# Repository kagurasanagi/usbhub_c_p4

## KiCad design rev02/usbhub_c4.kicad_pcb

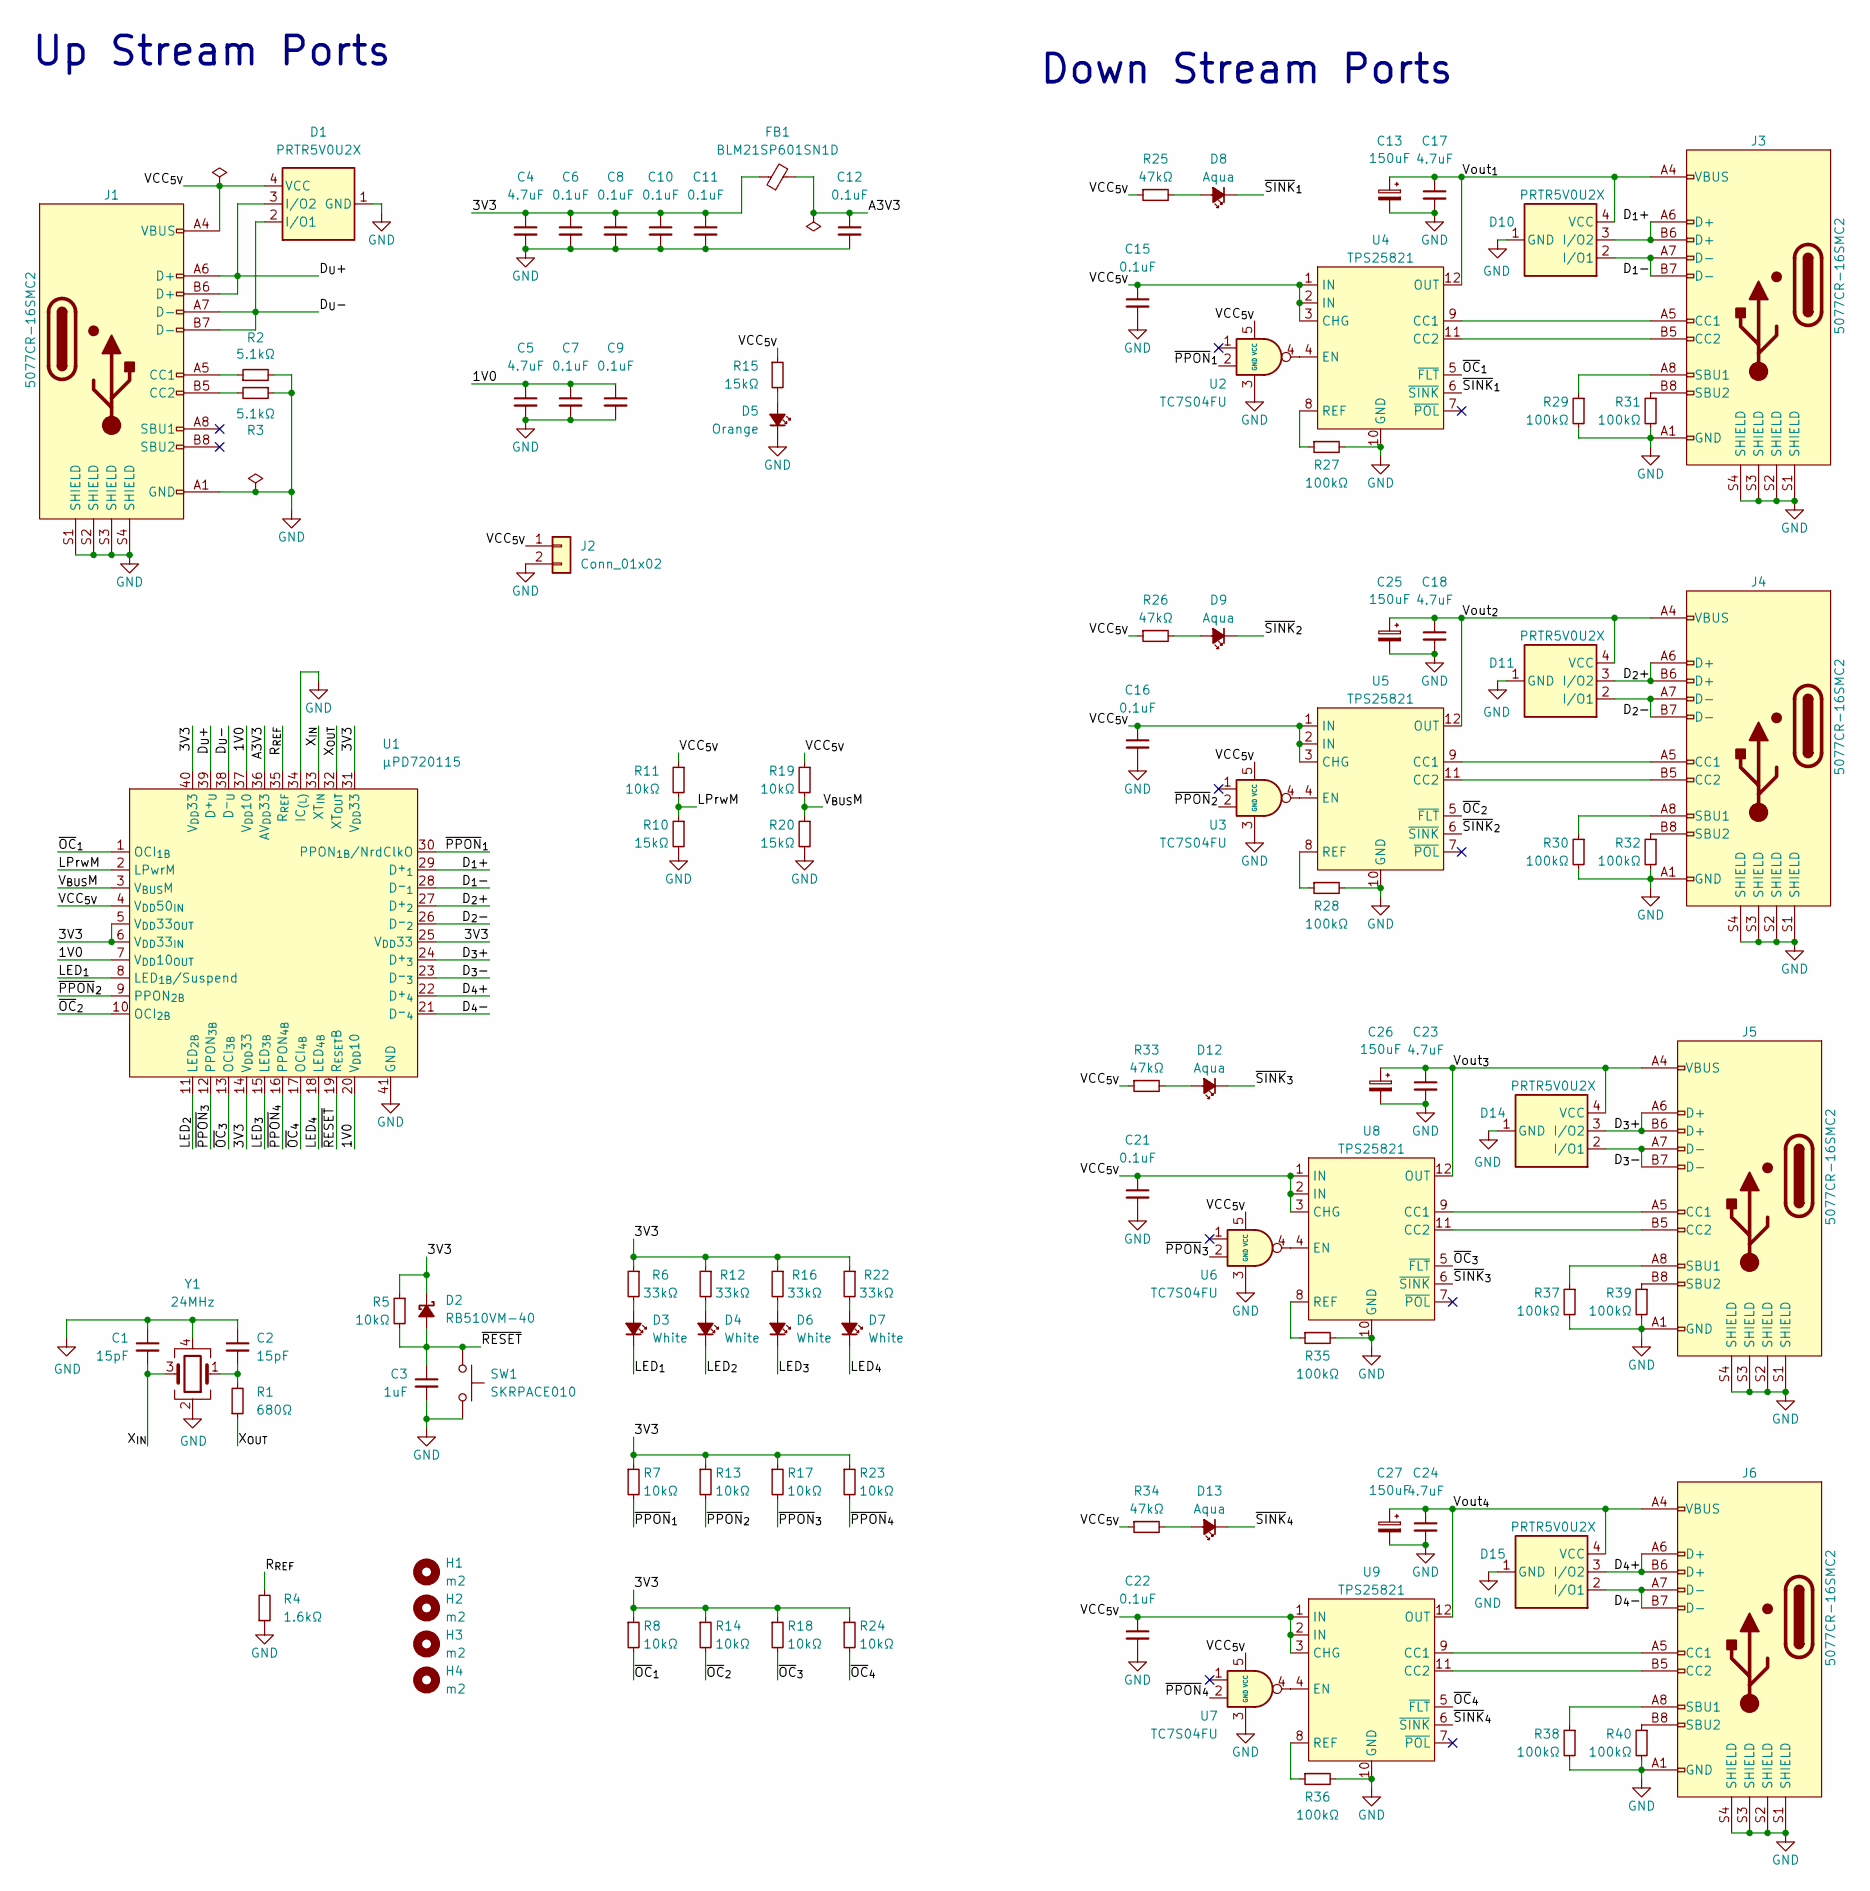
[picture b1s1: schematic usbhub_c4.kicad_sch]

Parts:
C1, C2: 15pF; C_0603_1608Metric
C3: 1uF; C_0603_1608Metric
C4, C5, C17, C18, C23, C24: 4.7uF; C_1206_3216Metric
C6, C7, C8, C9, C10, C11, C12: 0.1uF; C_0402_1005Metric
C13, C25, C26, C27: 150uF; CP_Radial_D6.3mm_P2.50mm
C15, C16, C21, C22: 0.1uF; C_0603_1608Metric
D1, D10, D11, D14, D15: PRTR5V0U2X; SOT-143
D2: RB510VM-40; Rohm_UMD2
D3, D4, D6, D7: White; LED_0603_1608Metric
D5: Orange; LED_0603_1608Metric
D8, D9, D12, D13: Aqua; LED_0603_1608Metric
FB1: BLM21SP601SN1D; R_0805_2012Metric
H1, H2, H3, H4: m2; MountingHole_2.2mm
J1, J3, J4, J5, J6: 5077CR-16SMC2; USB_C_Receptacle_5077CR-16SMC2
J2: Conn_01x02; JST_PH_B2B-PH-K_1x02_P2.00mm_Vertical
R1: 680Ω; R_0402_1005Metric
R2, R3: 5.1kΩ; R_0603_1608Metric
R4: 1.6kΩ; R_0402_1005Metric
R5, R11, R19: 10kΩ; R_0603_1608Metric
R6, R12, R16, R22: 33kΩ; R_0603_1608Metric
R7, R8, R13, R14, R17, R18, R23, R24: 10kΩ; R_0402_1005Metric
R10, R15, R20: 15kΩ; R_0603_1608Metric
R25, R26, R33, R34: 47kΩ; R_0603_1608Metric
R27, R28, R29, R30, R31, R32, R35, R36, R37, R38, R39, R40: 100kΩ; R_0603_1608Metric
SW1: SKRPACE010; SW_Push_1P1T_alps_SKRP
U1: μPD720115; QFN-40-1EP_6x6mm_P0.5mm_EP4.6x4.6mm
U2, U3, U6, U7: TC7S04FU; SOT-353_SC-70-5
U4, U5, U8, U9: TPS25821; WSON-12-1EP_3x2mm_P0.5mm_EP1x2.65_ThermalVias
Y1: 24MHz; Crystal_SMD_SeikoEpson_TSX3225-4Pin_3.2x2.5mm

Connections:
/1V0: C5.1, C7.1, C9.1, U1.7 (V_{DD}10_{OUT}), U1.20 (V_{DD}10), U1.37 (V_{DD}10)
/3V3: C4.1, C6.1, C8.1, C10.1, C11.1, D2.1 (K), FB1.1, R5.1, R6.1, R7.1, R8.1, R12.1, R13.1, R14.1, R16.1, R17.1, R18.1, R22.1, R23.1, R24.1, U1.5 (V_{DD}33_{OUT}), U1.6 (V_{DD}33_{IN}), U1.14 (V_{DD}33), U1.25 (V_{DD}33), U1.31 (V_{DD}33), U1.40 (V_{DD}33)
/A3V3: C12.1, FB1.2, U1.36 (AV_{DD}33)
/D_{1}+: D10.3 (I/O2), J3.A6 (D+), J3.B6 (D+), U1.29 (D^{+}_{1})
/D_{1}-: D10.2 (I/O1), J3.A7 (D-), J3.B7 (D-), U1.28 (D^{-}_{1})
/D_{2}+: D11.3 (I/O2), J4.A6 (D+), J4.B6 (D+), U1.27 (D^{+}_{2})
/D_{2}-: D11.2 (I/O1), J4.A7 (D-), J4.B7 (D-), U1.26 (D^{-}_{2})
/D_{3}+: D14.3 (I/O2), J5.A6 (D+), J5.B6 (D+), U1.24 (D^{+}_{3})
/D_{3}-: D14.2 (I/O1), J5.A7 (D-), J5.B7 (D-), U1.23 (D^{-}_{3})
/D_{4}+: D15.3 (I/O2), J6.A6 (D+), J6.B6 (D+), U1.22 (D^{+}_{4})
/D_{4}-: D15.2 (I/O1), J6.A7 (D-), J6.B7 (D-), U1.21 (D^{-}_{4})
/D_{U}+: D1.3 (I/O2), J1.A6 (D+), J1.B6 (D+), U1.39 (D^{+}_{U})
/D_{U}-: D1.2 (I/O1), J1.A7 (D-), J1.B7 (D-), U1.38 (D^{-}_{U})
/LED_{1}: D3.1 (K), U1.8 (LED_{1B}/Suspend)
/LED_{2}: D4.1 (K), U1.11 (LED_{2B})
/LED_{3}: D6.1 (K), U1.15 (LED_{3B})
/LED_{4}: D7.1 (K), U1.18 (LED_{4B})
/LPrwM: R10.1, R11.2, U1.2 (LPwrM)
/R_{REF}: R4.2, U1.35 (R_{REF})
/VCC_{5V}: C15.1, C16.1, C21.1, C22.1, D1.4 (VCC), J1.A4 (VBUS), J1.B4 (VBUS), J2.1, R11.1, R15.1, R19.1, R25.1, R26.1, R33.1, R34.1, U1.4 (V_{DD}50_{IN}), U2.5 (VCC), U3.5 (VCC), U4.1 (IN), U4.2 (IN), U4.3 (CHG), U5.1 (IN), U5.2 (IN), U5.3 (CHG), U6.5 (VCC), U7.5 (VCC), U8.1 (IN), U8.2 (IN), U8.3 (CHG), U9.1 (IN), U9.2 (IN), U9.3 (CHG)
/V_{BUS}M: R19.2, R20.1, U1.3 (V_{BUS}M)
/Vout_{1}: C13.1, C17.1, D10.4 (VCC), J3.A4 (VBUS), J3.B4 (VBUS), U4.12 (OUT)
/Vout_{2}: C18.1, C25.1, D11.4 (VCC), J4.A4 (VBUS), J4.B4 (VBUS), U5.12 (OUT)
/Vout_{3}: C23.1, C26.1, D14.4 (VCC), J5.A4 (VBUS), J5.B4 (VBUS), U8.12 (OUT)
/Vout_{4}: C24.1, C27.1, D15.4 (VCC), J6.A4 (VBUS), J6.B4 (VBUS), U9.12 (OUT)
/X_{IN}: C1.2, U1.33 (XT_{IN}), Y1.3
/X_{OUT}: R1.1, U1.32 (XT_{OUT})
/~OC_{1}: R8.2, U1.1 (OCI_{1B}), U4.5 (~FLT)
/~OC_{2}: R14.2, U1.10 (OCI_{2B}), U5.5 (~FLT)
/~OC_{3}: R18.2, U1.13 (OCI_{3B}), U8.5 (~FLT)
/~OC_{4}: R24.2, U1.17 (OCI_{4B}), U9.5 (~FLT)
/~PPON_{1}: R7.2, U1.30 (PPON_{1B}/NrdClkO), U2.2
/~PPON_{2}: R13.2, U1.9 (PPON_{2B}), U3.2
/~PPON_{3}: R17.2, U1.12 (PPON_{3B}), U6.2
/~PPON_{4}: R23.2, U1.16 (PPON_{4B}), U7.2
/~RESET: C3.1, D2.2 (A), R5.2, SW1.1, U1.19 (R_{ESET}B)
/~SINK_{1}: D8.1 (K), U4.6 (~SINK)
/~SINK_{2}: D9.1 (K), U5.6 (~SINK)
/~SINK_{3}: D12.1 (K), U8.6 (~SINK)
/~SINK_{4}: D13.1 (K), U9.6 (~SINK)
GND: C1.1, C2.1, C3.2, C4.2, C5.2, C6.2, C7.2, C8.2, C9.2, C10.2, C11.2, C12.2, C13.2, C15.2, C16.2, C17.2, C18.2, C21.2, C22.2, C23.2, C24.2, C25.2, C26.2, C27.2, D1.1 (GND), D5.1 (K), D10.1 (GND), D11.1 (GND), D14.1 (GND), D15.1 (GND), J1.A1 (GND), J1.B1 (GND), J1.S1 (SHIELD), J1.S2 (SHIELD), J1.S3 (SHIELD), J1.S4 (SHIELD), J2.2, J3.A1 (GND), J3.B1 (GND), J3.S1 (SHIELD), J3.S2 (SHIELD), J3.S3 (SHIELD), J3.S4 (SHIELD), J4.A1 (GND), J4.B1 (GND), J4.S1 (SHIELD), J4.S2 (SHIELD), J4.S3 (SHIELD), J4.S4 (SHIELD), J5.A1 (GND), J5.B1 (GND), J5.S1 (SHIELD), J5.S2 (SHIELD), J5.S3 (SHIELD), J5.S4 (SHIELD), J6.A1 (GND), J6.B1 (GND), J6.S1 (SHIELD), J6.S2 (SHIELD), J6.S3 (SHIELD), J6.S4 (SHIELD), R2.2, R3.1, R4.1, R10.2, R20.2, R27.2, R28.2, R29.2, R30.2, R31.2, R32.2, R35.2, R36.2, R37.2, R38.2, R39.2, R40.2, SW1.2, U1.34 (IC_{(L)}), U1.41 (GND), U2.3 (GND), U3.3 (GND), U4.10 (GND), U4.13 (GND), U5.10 (GND), U5.13 (GND), U6.3 (GND), U7.3 (GND), U8.10 (GND), U8.13 (GND), U9.10 (GND), U9.13 (GND), Y1.2, Y1.4
unnamed: C2.2, R1.2, Y1.1
unnamed: D3.2 (A), R6.2
unnamed: D4.2 (A), R12.2
unnamed: D5.2 (A), R15.2
unnamed: D6.2 (A), R16.2
unnamed: D7.2 (A), R22.2
unnamed: D8.2 (A), R25.2
unnamed: D9.2 (A), R26.2
unnamed: D12.2 (A), R33.2
unnamed: D13.2 (A), R34.2
unnamed: J1.A5 (CC1), R2.1
unnamed: J1.B5 (CC2), R3.2
unnamed: J3.A5 (CC1), U4.9 (CC1)
unnamed: J3.B5 (CC2), U4.11 (CC2)
unnamed: J3.A8 (SBU1), R29.1
unnamed: J3.B8 (SBU2), R31.1
unnamed: J4.A5 (CC1), U5.9 (CC1)
unnamed: J4.B5 (CC2), U5.11 (CC2)
unnamed: J4.A8 (SBU1), R30.1
unnamed: J4.B8 (SBU2), R32.1
unnamed: J5.A5 (CC1), U8.9 (CC1)
unnamed: J5.B5 (CC2), U8.11 (CC2)
unnamed: J5.A8 (SBU1), R37.1
unnamed: J5.B8 (SBU2), R39.1
unnamed: J6.A5 (CC1), U9.9 (CC1)
unnamed: J6.B5 (CC2), U9.11 (CC2)
unnamed: J6.A8 (SBU1), R38.1
unnamed: J6.B8 (SBU2), R40.1
unnamed: U2.4, U4.4 (EN)
unnamed: R27.1, U4.8 (REF)
unnamed: U3.4, U5.4 (EN)
unnamed: R28.1, U5.8 (REF)
unnamed: U6.4, U8.4 (EN)
unnamed: R35.1, U8.8 (REF)
unnamed: U7.4, U9.4 (EN)
unnamed: R36.1, U9.8 (REF)

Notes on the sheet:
Up Stream Ports
Down Stream Ports

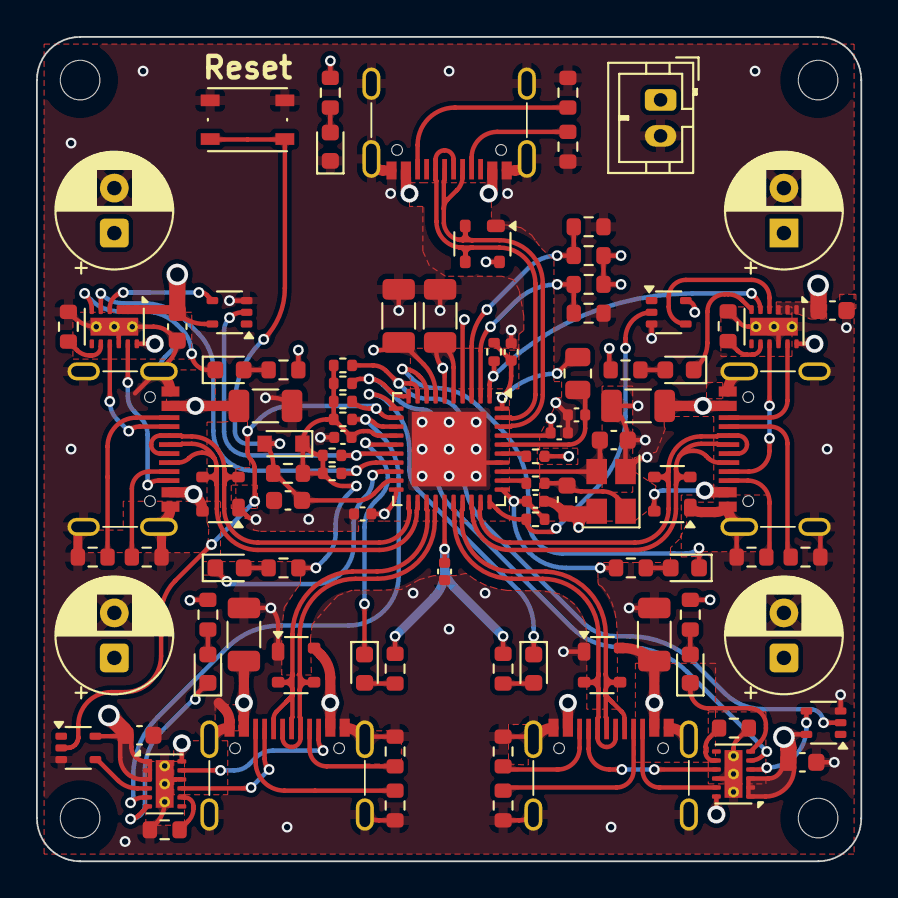
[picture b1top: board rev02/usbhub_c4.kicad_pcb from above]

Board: 4 copper layers, 45.8 x 45.8 mm, 99 parts (0 on the bottom side), 77 nets.

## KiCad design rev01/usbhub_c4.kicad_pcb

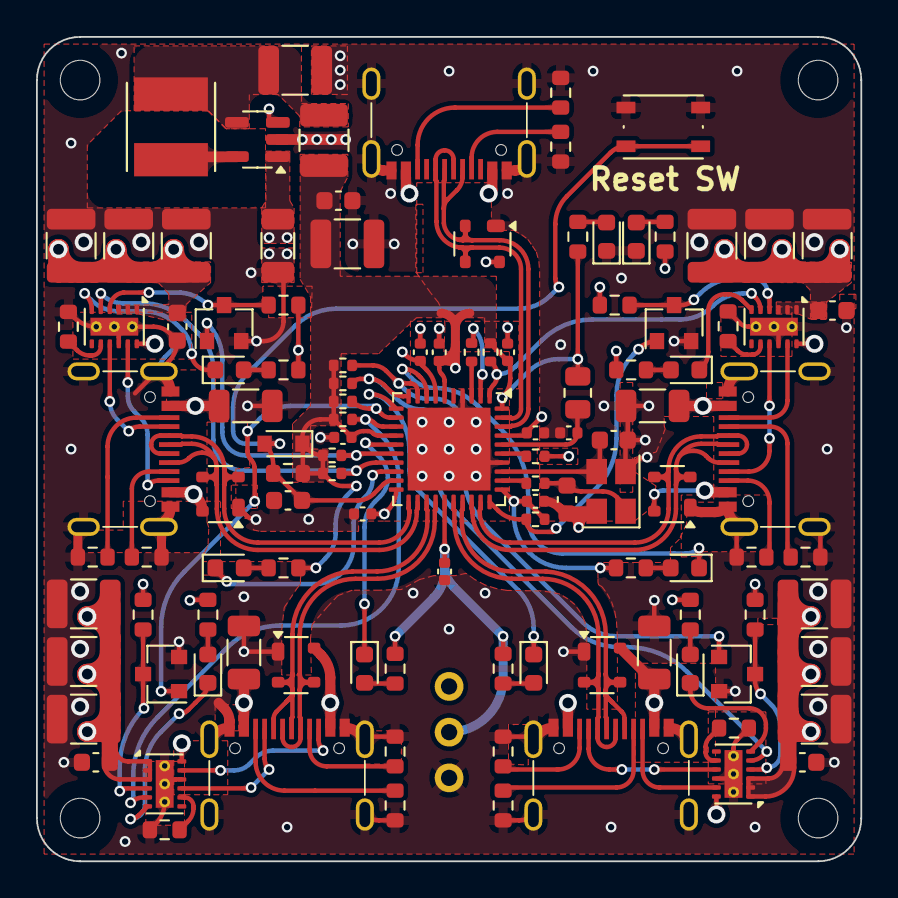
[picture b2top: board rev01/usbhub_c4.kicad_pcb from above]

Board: 4 copper layers, 45.8 x 45.8 mm, 119 parts (0 on the bottom side), 79 nets.

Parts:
C1, C21, C26, C31, C36: 4.7uF; C_1206_3216Metric
C2, C3, C17, C18, C19, C22, C23, C24, C27, C28, C29, C32, C33, C34: 47uF; C_1210_3225Metric
C4, C20, C25, C30, C35: 0.1uF; C_0603_1608Metric
C5, C6: 15pF; C_0603_1608Metric
C7: 1uF; C_0603_1608Metric
C8, C14: 4.7uF; C_0402_1005Metric
C9, C10, C11, C12, C13, C15, C16: 0.1uF; C_0402_1005Metric
D1, D10, D12, D14, D16: PRTR5V0U2X; SOT-143
D2: Orange; LED_0603_1608Metric
D3: Green; LED_0603_1608Metric
D4: RB510VM-40; Rohm_UMD2
D5, D6, D7, D8: White; LED_0603_1608Metric
D9, D11, D13, D15: WarmWhite; LED_0603_1608Metric
FB1: BLM21SP601SN1D; R_0805_2012Metric
H1, H2, H3, H4: m2; MountingHole_2.2mm
J1, J5, J6, J7, J8: 5077CR-16SMC2; USB_C_Receptacle_5077CR-16SMC2
J2, J3, J4: Conn_01x01; PinHeader_1x01_P2.54mm_Vertical
L1: 10uH; IND_LQH5BPN100M38L
L2: 1uH; L_1210_3225Metric
Q1, Q2, Q3, Q4: BSS138; SOT-23
R1, R2: 5.1kΩ; R_0603_1608Metric
R3: 15kΩ; R_0603_1608Metric
R4, R21, R26, R31, R36: 47kΩ; R_0603_1608Metric
R5: 680Ω; R_0402_1005Metric
R6: 10kΩ; R_0603_1608Metric
R7, R8, R9, R10: 33kΩ; R_0603_1608Metric
R11, R12, R13, R14, R15, R16, R17, R18, R19: 10kΩ; R_0402_1005Metric
R20: 1.6kΩ; R_0402_1005Metric
R22, R23, R24, R25, R27, R28, R29, R30, R32, R33, R34, R35, R37, R38, R39, R40: 100kΩ; R_0603_1608Metric
SW1: SKRPACE010; SW_Push_1P1T_alps_SKRP
U1: LM3670MF-3.3; TSOT-23-5
U2: μPD720115; QFN-40-1EP_6x6mm_P0.5mm_EP4.6x4.6mm
U3, U4, U5, U6: TPS25821; WSON-12-1EP_3x2mm_P0.5mm_EP1x2.65_ThermalVias
Y1: 24MHz; Crystal_SMD_SeikoEpson_TSX3225-4Pin_3.2x2.5mm

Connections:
/1V0: C14.1, C15.1, C16.1, U2.7 (V_{DD}10_{OUT}), U2.20 (V_{DD}10), U2.37 (V_{DD}10)
/3V3: C3.1, C4.1, C8.1, C9.1, C10.1, C11.1, C12.1, D4.1 (K), FB1.1, J3.1, L2.2, R4.1, R6.1, R7.1, R8.1, R9.1, R10.1, R11.1, R12.1, R13.1, R14.1, R15.1, R16.1, R17.1, R18.1, U2.6 (V_{DD}33_{IN}), U2.14 (V_{DD}33), U2.25 (V_{DD}33), U2.31 (V_{DD}33), U2.40 (V_{DD}33)
/A3V3: C13.1, FB1.2, U2.36 (AV_{DD}33)
/D_{1}+: D10.3 (I/O2), J5.A6 (D+), J5.B6 (D+), U2.29 (D^{+}_{1})
/D_{1}-: D10.2 (I/O1), J5.A7 (D-), J5.B7 (D-), U2.28 (D^{-}_{1})
/D_{2}+: D12.3 (I/O2), J6.A6 (D+), J6.B6 (D+), U2.27 (D^{+}_{2})
/D_{2}-: D12.2 (I/O1), J6.A7 (D-), J6.B7 (D-), U2.26 (D^{-}_{2})
/D_{3}+: D14.3 (I/O2), J7.A6 (D+), J7.B6 (D+), U2.24 (D^{+}_{3})
/D_{3}-: D14.2 (I/O1), J7.A7 (D-), J7.B7 (D-), U2.23 (D^{-}_{3})
/D_{4}+: D16.3 (I/O2), J8.A6 (D+), J8.B6 (D+), U2.22 (D^{+}_{4})
/D_{4}-: D16.2 (I/O1), J8.A7 (D-), J8.B7 (D-), U2.21 (D^{-}_{4})
/D_{U}+: D1.3 (I/O2), J1.A6 (D+), J1.B6 (D+), U2.39 (D^{+}_{U})
/D_{U}-: D1.2 (I/O1), J1.A7 (D-), J1.B7 (D-), U2.38 (D^{-}_{U})
/LED_{1}: D5.1 (K), U2.8 (LED_{1B}/Suspend)
/LED_{2}: D6.1 (K), U2.11 (LED_{2B})
/LED_{3}: D7.1 (K), U2.15 (LED_{3B})
/LED_{4}: D8.1 (K), U2.18 (LED_{4B})
/R_{REF}: R20.2, U2.35 (R_{REF})
/VCC_{5V}: C1.1, C17.1, C18.1, C19.1, C20.1, C22.1, C23.1, C24.1, C25.1, C27.1, C28.1, C29.1, C30.1, C32.1, C33.1, C34.1, C35.1, D1.4 (VCC), J1.A4 (VBUS), J1.B4 (VBUS), J2.1, R3.1, R19.1, R21.1, R22.2, R26.1, R27.2, R31.1, R32.2, R36.1, R37.2, U1.1 (Vin), U1.3 (EN), U2.2 (LPwrM), U3.1 (IN), U3.2 (IN), U3.3 (CHG), U4.1 (IN), U4.2 (IN), U4.3 (CHG), U5.1 (IN), U5.2 (IN), U5.3 (CHG), U6.1 (IN), U6.2 (IN), U6.3 (CHG)
/V_{BUS}M: R19.2, U2.3 (V_{BUS}M)
/Vout_{1}: C21.1, D10.4 (VCC), J5.A4 (VBUS), J5.B4 (VBUS), U3.12 (OUT)
/Vout_{2}: C26.1, D12.4 (VCC), J6.A4 (VBUS), J6.B4 (VBUS), U4.12 (OUT)
/Vout_{3}: C31.1, D14.4 (VCC), J7.A4 (VBUS), J7.B4 (VBUS), U5.12 (OUT)
/Vout_{4}: C36.1, D16.4 (VCC), J8.A4 (VBUS), J8.B4 (VBUS), U6.12 (OUT)
/X_{IN}: C5.2, U2.33 (XT_{IN}), Y1.3
/X_{OUT}: R5.1, U2.32 (XT_{OUT})
/~OC_{1}: R15.2, U2.1 (OCI_{1B}), U3.5 (~FLT)
/~OC_{2}: R16.2, U2.10 (OCI_{2B}), U4.5 (~FLT)
/~OC_{3}: R17.2, U2.13 (OCI_{3B}), U5.5 (~FLT)
/~OC_{4}: R18.2, U2.17 (OCI_{4B}), U6.5 (~FLT)
/~PPON_{1}: Q1.1 (G), R11.2, U2.30 (PPON_{1B}/NrdClkO)
/~PPON_{2}: Q2.1 (G), R12.2, U2.9 (PPON_{2B})
/~PPON_{3}: Q3.1 (G), R13.2, U2.12 (PPON_{3B})
/~PPON_{4}: Q4.1 (G), R14.2, U2.16 (PPON_{4B})
/~RESET: C7.1, D4.2 (A), R6.2, SW1.1, U2.19 (R_{ESET}B)
/~SINK_{1}: D9.1 (K), U3.6 (~SINK)
/~SINK_{2}: D11.1 (K), U4.6 (~SINK)
/~SINK_{3}: D13.1 (K), U5.6 (~SINK)
/~SINK_{4}: D15.1 (K), U6.6 (~SINK)
GND: C1.2, C2.2, C3.2, C4.2, C5.1, C6.1, C7.2, C8.2, C9.2, C10.2, C11.2, C12.2, C13.2, C14.2, C15.2, C16.2, C17.2, C18.2, C19.2, C20.2, C21.2, C22.2, C23.2, C24.2, C25.2, C26.2, C27.2, C28.2, C29.2, C30.2, C31.2, C32.2, C33.2, C34.2, C35.2, C36.2, D1.1 (GND), D2.1 (K), D3.1 (K), D10.1 (GND), D12.1 (GND), D14.1 (GND), D16.1 (GND), J1.A1 (GND), J1.B1 (GND), J1.S1 (SHIELD), J1.S2 (SHIELD), J1.S3 (SHIELD), J1.S4 (SHIELD), J4.1, J5.A1 (GND), J5.B1 (GND), J5.S1 (SHIELD), J5.S2 (SHIELD), J5.S3 (SHIELD), J5.S4 (SHIELD), J6.A1 (GND), J6.B1 (GND), J6.S1 (SHIELD), J6.S2 (SHIELD), J6.S3 (SHIELD), J6.S4 (SHIELD), J7.A1 (GND), J7.B1 (GND), J7.S1 (SHIELD), J7.S2 (SHIELD), J7.S3 (SHIELD), J7.S4 (SHIELD), J8.A1 (GND), J8.B1 (GND), J8.S1 (SHIELD), J8.S2 (SHIELD), J8.S3 (SHIELD), J8.S4 (SHIELD), Q1.2 (S), Q2.2 (S), Q3.2 (S), Q4.2 (S), R1.2, R2.1, R20.1, R23.2, R24.2, R25.2, R28.2, R29.2, R30.2, R33.2, R34.2, R35.2, R38.2, R39.2, R40.2, SW1.2, U1.2 (GND), U2.4 (V_{DD}50_{IN}), U2.34 (IC_{(L)}), U2.41 (GND), U3.10 (GND), U3.13 (GND), U4.10 (GND), U4.13 (GND), U5.10 (GND), U5.13 (GND), U6.10 (GND), U6.13 (GND), Y1.2, Y1.4
unnamed: C6.2, R5.2, Y1.1
unnamed: D2.2 (A), R3.2
unnamed: D3.2 (A), R4.2
unnamed: D5.2 (A), R7.2
unnamed: D6.2 (A), R8.2
unnamed: D7.2 (A), R9.2
unnamed: D8.2 (A), R10.2
unnamed: D9.2 (A), R21.2
unnamed: D11.2 (A), R26.2
unnamed: D13.2 (A), R31.2
unnamed: D15.2 (A), R36.2
unnamed: J1.A5 (CC1), R1.1
unnamed: J1.B5 (CC2), R2.2
unnamed: J5.A5 (CC1), U3.9 (CC1)
unnamed: J5.B5 (CC2), U3.11 (CC2)
unnamed: J5.A8 (SBU1), R24.1
unnamed: J5.B8 (SBU2), R25.1
unnamed: J6.A5 (CC1), U4.9 (CC1)
unnamed: J6.B5 (CC2), U4.11 (CC2)
unnamed: J6.A8 (SBU1), R29.1
unnamed: J6.B8 (SBU2), R30.1
unnamed: J7.A5 (CC1), U5.9 (CC1)
unnamed: J7.B5 (CC2), U5.11 (CC2)
unnamed: J7.A8 (SBU1), R34.1
unnamed: J7.B8 (SBU2), R35.1
unnamed: J8.A5 (CC1), U6.9 (CC1)
unnamed: J8.B5 (CC2), U6.11 (CC2)
unnamed: J8.A8 (SBU1), R39.1
unnamed: J8.B8 (SBU2), R40.1
unnamed: Q1.3 (D), R22.1, U3.4 (EN)
unnamed: Q2.3 (D), R27.1, U4.4 (EN)
unnamed: Q3.3 (D), R32.1, U5.4 (EN)
unnamed: Q4.3 (D), R37.1, U6.4 (EN)
unnamed: C2.1, L1.2, L2.1, U1.4 (FB)
unnamed: L1.1, U1.5 (SW)
unnamed: R23.1, U3.8 (REF)
unnamed: R28.1, U4.8 (REF)
unnamed: R33.1, U5.8 (REF)
unnamed: R38.1, U6.8 (REF)

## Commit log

2025-05-08 rev01
2025-05-25 シンプル版追加
2025-06-15 ダウンストリームポートキャパシタを高分子コンデンサに変更
2025-06-15 ダウンストリームポートキャパシタをコールドになる位置に変更
2025-07-13 Add teardrops and update routing in USB hub PCB
    Added teardrops to multiple pads and vias in rev02/usbhub_c4.kicad_pcb for improved manufacturability. Updated several net routings, modified some arc and segment connections, and made minor schemati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
